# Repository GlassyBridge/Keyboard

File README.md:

<h1 align="center"> MK-1000 </h1>
<h4 align="center">A Modular-Wireless Keyboard </h4>
<div align="center">
  
</div>
<p align="center">A fully custom modular keyboard that has both wireless and wired capabilities, uses MX hotswap switches (with per key RGB lighting) and magnetic pogo pin connectors with I2C protocol.</p>
<h2></h2>
<h2> Features </h2>

- Works over USB-C (wired) or Bluetooth (wireless)
- Integrated magnetic pogo pins for stable I2C connection and adding external modules (numberpads, macropads or OLED modules)
- Integrated charging circuit for portability and wireless operation
- Uses MX hotswap sockets for key switch connections
- Features SK6812MINI-E back mounted LEDs for customizable per key RGB lighting
- Includes a dedicated SWD interface for debugging and development
- A dedicated slide switch to manage battery life

<h2> Why this project? </h2>

This project was made as an attempt to tackle more complex hardware from my previous projects. I spent a lot of time designing and reiterating it and its purpose is simple. I made it to function as a plug and play device that has modular capabilities.

I also wanted a cool looking keyboard so I added features I liked into this one big project.

<h2>Design</h2>
<h3>Schematic</h3>

<h4 align="center">Main board & Keypad</h4>
<h3>PCB</h3>

<h4 align="center">PCB back</h4>

<h4 align="center">PCB front</h4>

<h4 align="center">PCB</h4>

<h4 align="center">PCB 3D model</h4>

<h4 align="center">PCB 3D model with components</h4>

<h4 align="center">Wiring Diagram</h4>

<h2>Firmware</h2>

Available in the `Firmware` folder. (Basic version for now. I'll update it once I built the keyboard)
<h2>Bill of Materials</h2>

| Name                     | Reference   |    Qty     | moq | Price ($) | Shipping   |                                            Link                                             |
| ------------------------ | ----------- | :--------: | --- | --------- | ---------- | :-----------------------------------------------------------------------------------------: |
| OLED Screens (128X32)    | Brd11       |     1      | 1   | 2.42      | Aliexpress |             [Aliexpress](https://www.aliexpress.us/item/3256806165075447.html)              |
| ------------ (128X64)    | Brd12       |     1      | 1   | 4.18      | Aliexpress |             [Aliexpress](https://www.aliexpress.us/item/3256810159598938.html)              |
| 1X6 Magnetic Pogo Pins   | Conn1-Conn8 | 8(4 pairs) | 5p  | 25.25     | Aliexpress |             [Aliexpress](https://www.aliexpress.us/item/3256805098127227.html)              |
| Capacitors (10uF)        | C1-C4       |     4      | 20  | 0.43      | LCSC       |                  [C15850](https://www.lcsc.com/product-detail/C15850.html)                  |
| ---------- (4.7uF)       | C5,C6       |     2      | 20  | 0.29      | LCSC       |                   [C1779](https://www.lcsc.com/product-detail/C1779.html)                   |
| ---------- (22uF)        | C7,C8       |     2      | 20  | 1.12      | LCSC       |                  [C12891](https://www.lcsc.com/product-detail/C12891.html)                  |
| Diodes                   | D1-D99      |     99     | 100 | 0.93      | LCSC       |                   [C2099](https://www.lcsc.com/product-detail/C2099.html)                   |
| ---------- (SS34)        | SS34        |     1      | 20  | 0.56      | LCSC       |                 [C908680](https://www.lcsc.com/product-detail/C908680.html)                 |
| ESDA5V3L                 | ESD1,ESD2   |     2      | 10  | 0.39      | LCSC       |                 [C587142](https://www.lcsc.com/product-detail/C587142.html)                 |
| USB Connector            | J1          |     1      | 5   | 0.84      | LCSC       |                 [C165948](https://www.lcsc.com/product-detail/C165948.html)                 |
| 2x3 1mm PinHeader        | J2          |     1      | 20  | 0.65      | LCSC       |                [C6837603](https://www.lcsc.com/product-detail/C6837603.html)                |
| Inductors  (10uH)        | L1          |     1      | 10  | 0.47      | LCSC       |                  [C88173](https://www.lcsc.com/product-detail/C88173.html)                  |
| ---------- (22uH)        | L2          |     1      | 5   | 0.83      | LCSC       |                  [C27442](https://www.lcsc.com/product-detail/C27442.html)                  |
| SK6812MINI-E (LEDs)      | LED1-LED99  |     99     | 100 | 7.45      | LCSC       |                [C5149201](https://www.lcsc.com/product-detail/C5149201.html)                |
| P_Mosfets                | Q1-Q3       |     3      | 10  | 0.65      | LCSC       |                  [C10487](https://www.lcsc.com/product-detail/C10487.html)                  |
| Resistors  (110K)        | R1          |     2      | 100 | 0.19      | LCSC       |                [C2907221](https://www.lcsc.com/product-detail/C2907221.html)                |
| ---------- (5K1)         | R2,R4       |     2      | 100 | 0.24      | LCSC       |                  [C27834](https://www.lcsc.com/product-detail/C27834.html)                  |
| ---------- (100K)        | R3,R5,R6    |     2      | 100 | 0.22      | LCSC       |                [C2933502](https://www.lcsc.com/product-detail/C2933502.html)                |
| ---------- (4K7)         | R7,R12,R18  |     4      | 100 | 0.19      | LCSC       |                  [C17673](https://www.lcsc.com/product-detail/C17673.html)                  |
| ---------- (27R)         | R8,R11      |     2      | 100 | 0.22      | LCSC       |                  [C17594](https://www.lcsc.com/product-detail/C17594.html)                  |
| ---------- (806K)        | R9,R16,R21  |     3      | 100 | 0.22      | LCSC       |                [C2933502](https://www.lcsc.com/product-detail/C2933502.html)                |
| ---------- (2M)          | R10,R17,R22 |     3      | 100 | 0.30      | LCSC       |                  [C26112](https://www.lcsc.com/product-detail/C26112.html)                  |
| ---------- (15K)         | R13         |     1      | 100 | 0.21      | LCSC       |                [C2930170](https://www.lcsc.com/product-detail/C2930170.html)                |
| ---------- (10K)         | R14,R19     |     2      | 100 | 0.25      | LCSC       |                  [C17414](https://www.lcsc.com/product-detail/C17414.html)                  |
| ---------- (2K)          | R15         |     1      | 100 | 0.25      | LCSC       |                  [C17604](https://www.lcsc.com/product-detail/C17604.html)                  |
| Rotary Encoder           | RE1         |     1      | 1   | 1.87      | LCSC       |                 [C470742](https://www.lcsc.com/product-detail/C470742.html)                 |
| Slide switch (1825232-1) | SPDT1       |     1      | 1   | 0.93      | LCSC       |                [C5167252](https://www.lcsc.com/product-detail/C5167252.html)                |
| MT3608                   | U1          |     1      | 10  | 0.79      | LCSC       |                  [C84817](https://www.lcsc.com/product-detail/C84817.html)                  |
| USB6B1                   | U2          |     1      | 1   | 0.47      | LCSC       |                 [C283483](https://www.lcsc.com/product-detail/C283483.html)                 |
| MDBT50Q-1MV2 (MCU)       | U3          |     1      | 1   | 10.10     | SEED       | [Seed Studio](https://www.seeedstudio.com/MDBT50Q-1M-nRF52840-Based-BLE-Module-p-3147.html) |
| MCP73831T-2ACI/OT        | U4          |     1      | 1   | 0.74      | LCSC       |                 [C424093](https://www.lcsc.com/product-detail/C424093.html)                 |
| XIAO-nRF52840-SMD (MCU)  | U5          |     1      | 1   | 9.90      | 3.75       |       [Seed Studio](https://www.seeedstudio.com/Seeed-XIAO-BLE-nRF52840-p-5201.html)        |
| MCP23017                 | U6          |     1      | 1   | 2.03      | LCSC       |                 [C639770](https://www.lcsc.com/product-detail/C639770.html)                 |
| 74LV1T08GV               | U7,U8       |     2      | 1   | 2.12      | LCSC       |                 [C547934](https://www.lcsc.com/product-detail/C547934.html)                 |
| Keys ----- (Sockets)     | SW1-SW99    |     99     | 110 | 8.18      | Aliexpress |             [Aliexpress](https://www.aliexpress.us/item/3256809001207500.html)              |
| ---------- (Switches)    | -           |     99     | 105 | 21.85 (T) | Aliexpress |             [Aliexpress](https://www.aliexpress.us/item/3256807647145642.html)              |
| ---------- (Key Caps)    | -           |     99     | -   | 7.48 (T)  | Aliexpress |             [Aliexpress](https://www.aliexpress.us/item/3256808975886837.html)              |
| ---------- (Stabilizers) | -           |     5      | -   | 5.78 (T)  | Aliexpress |             [Aliexpress](https://www.aliexpress.us/item/3256801499984864.html)              |
| lithium batteries        | -           |     2      | -   | 18.16 (T) | Aliexpress |             [Aliexpress](https://www.aliexpress.us/item/3256811743915654.html)              |

> *T for total price

| Supplier   | cost  | Shipping | Total cost |
| ---------- | ----- | -------- | ---------- |
| LCSC       | 24.65 | 13.08    | 37.73      |
| Aliexpress | 93.30 | 2.69     | 96.44      |
| SEED       | 20    | 8.55     | 28.55      |
| JLCPCB     | 29.90 | 20.14    | 50.04      |
| Total      | -     | -        | 212.76     |

<h2>Keyboard Case</h2>

A very basic case is provided in the `CAD` folder.

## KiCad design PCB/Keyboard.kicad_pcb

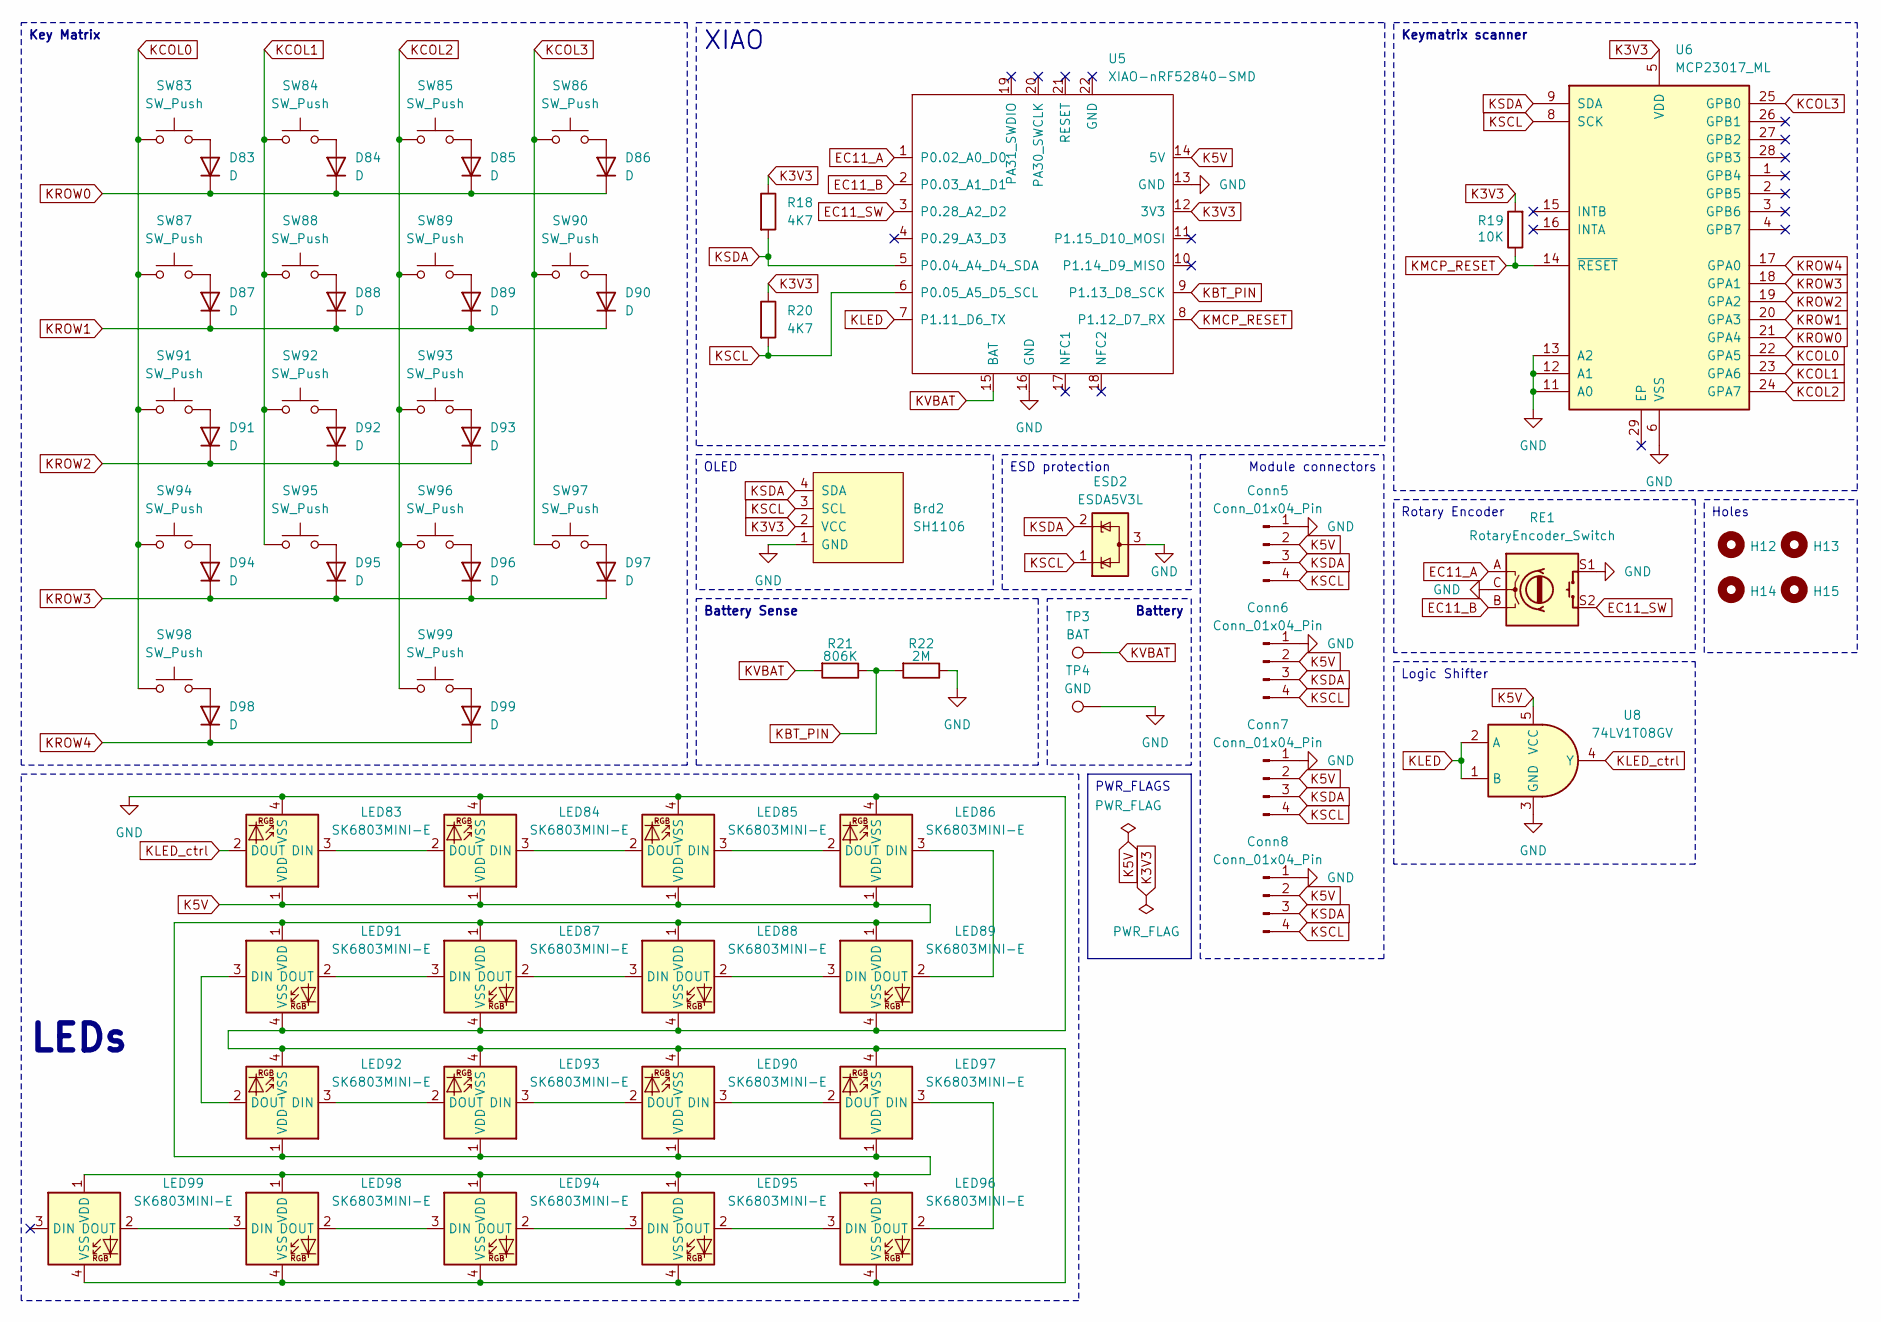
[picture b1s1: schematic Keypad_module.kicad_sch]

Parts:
Brd2: SH1106; 128x64OLED
Conn5, Conn7: Conn_01x04_Pin; Pogopin_Conn_1x4_Female
Conn6, Conn8: Conn_01x04_Pin; Pogopin_Conn_1x4_Male
D83, D84, D85, D86, D87, D88, D89, D90, D91, D92, D93, D94, D95, D96, D97, D98, D99: D; D_SOD-123; LCSC Part # C2099
ESD2: ESDA5V3L; SOT-23-3; LCSC Part # C587142
H12, H13, H14, H15: MountingHole; MountingHole_3.2mm_M3
LED83, LED84, LED85, LED86, LED87, LED88, LED89, LED90, LED91, LED92, LED93, LED94, LED95, LED96, LED97, LED98, LED99: SK6803MINI-E; LED
R18, R20: 4K7; R_0805_2012Metric; LCSC Part # C17673
R19: 10K; R_0805_2012Metric; LCSC Part # C17414
R21: 806K; R_0805_2012Metric; LCSC Part # C2933502
R22: 2M; R_0805_2012Metric; LCSC Part # C26112
RE1: RotaryEncoder_Switch; RotaryEncoder_Alps_EC11E-Switch_Vertical_H20mm_CircularMoun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
SW83, SW84, SW85, SW86, SW87, SW88, SW89, SW91, SW92, SW93, SW94, SW95, SW96, SW99: SW_Push; MX_HS_1u; LCSC Part # C5333465
SW90, SW97: SW_Push; MX_HS_2u_90deg; LCSC Part # C5333465
SW98: SW_Push; MX_HS_2u; LCSC Part # C5333465
TP3: BAT; TestPoint_Pad_D2.0mm
TP4: GND; TestPoint_Pad_D2.0mm
U5: XIAO-nRF52840-SMD; modified-XIAO-nRF52840-SMD; LCSC Part # C37327670
U6: MCP23017_ML; QFN-28-1EP_6x6mm_P0.65mm_EP4.25x4.25mm; LCSC Part # C639770
U8: 74LV1T08GV; SC-74A-5_1.55x2.9mm_P0.95mm

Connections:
EC11_A: RE1.A, U5.1 (P0.02_A0_D0)
EC11_B: RE1.B, U5.2 (P0.03_A1_D1)
EC11_SW: RE1.S2, U5.3 (P0.28_A2_D2)
GND: Brd2.1 (GND), Conn5.1, Conn6.1, Conn7.1, Conn8.1, ESD2.3 (A), LED83.4 (VSS), LED84.4 (VSS), LED85.4 (VSS), LED86.4 (VSS), LED87.4 (VSS), LED88.4 (VSS), LED89.4 (VSS), LED90.4 (VSS), LED91.4 (VSS), LED92.4 (VSS), LED93.4 (VSS), LED94.4 (VSS), LED95.4 (VSS), LED96.4 (VSS), LED97.4 (VSS), LED98.4 (VSS), LED99.4 (VSS), R22.1, RE1.C, RE1.S1, TP4.1, U5.13 (GND), U5.16 (GND), U6.6 (VSS), U6.11 (A0), U6.12 (A1), U6.13 (A2), U8.3 (GND); also elsewhere on the board
K3V3: Brd2.2 (VCC), R18.1, R19.2, R20.1, U5.12 (3V3), U6.5 (VDD)
K5V: Conn5.2, Conn6.2, Conn7.2, Conn8.2, LED83.1 (VDD), LED84.1 (VDD), LED85.1 (VDD), LED86.1 (VDD), LED87.1 (VDD), LED88.1 (VDD), LED89.1 (VDD), LED90.1 (VDD), LED91.1 (VDD), LED92.1 (VDD), LED93.1 (VDD), LED94.1 (VDD), LED95.1 (VDD), LED96.1 (VDD), LED97.1 (VDD), LED98.1 (VDD), LED99.1 (VDD), U5.14 (5V), U8.5 (VCC)
KBT_PIN: R21.1, R22.2, U5.9 (P1.13_D8_SCK)
KCOL0: SW83.1, SW87.1, SW91.1, SW94.1, SW98.1, U6.22 (GPA5)
KCOL1: SW84.1, SW88.1, SW92.1, SW95.1, U6.23 (GPA6)
KCOL2: SW85.1, SW89.1, SW93.1, SW96.1, SW99.1, U6.24 (GPA7)
KCOL3: SW86.1, SW90.1, SW97.1, U6.25 (GPB0)
KLED: U5.7 (P1.11_D6_TX), U8.1 (B), U8.2 (A)
KLED_ctrl: LED83.2 (DOUT), U8.4 (Y)
KMCP_RESET: R19.1, U5.8 (P1.12_D7_RX), U6.14 (~RESET)
KROW0: D83.1 (K), D84.1 (K), D85.1 (K), D86.1 (K), U6.21 (GPA4)
KROW1: D87.1 (K), D88.1 (K), D89.1 (K), D90.1 (K), U6.20 (GPA3)
KROW2: D91.1 (K), D92.1 (K), D93.1 (K), U6.19 (GPA2)
KROW3: D94.1 (K), D95.1 (K), D96.1 (K), D97.1 (K), U6.18 (GPA1)
KROW4: D98.1 (K), D99.1 (K), U6.17 (GPA0)
KSCL: Brd2.3 (SCL), Conn5.4, Conn6.4, Conn7.4, Conn8.4, ESD2.1 (K), R20.2, U5.6 (P0.05_A5_D5_SCL), U6.8 (SCK)
KSDA: Brd2.4 (SDA), Conn5.3, Conn6.3, Conn7.3, Conn8.3, ESD2.2 (K), R18.2, U5.5 (P0.04_A4_D4_SDA), U6.9 (SDA)
KVBAT: R21.2, TP3.1, U5.15 (BAT)
unnamed: D83.2 (A), SW83.2
unnamed: D84.2 (A), SW84.2
unnamed: D85.2 (A), SW85.2
unnamed: D86.2 (A), SW86.2
unnamed: D87.2 (A), SW87.2
unnamed: D88.2 (A), SW88.2
unnamed: D89.2 (A), SW89.2
unnamed: D90.2 (A), SW90.2
unnamed: D91.2 (A), SW91.2
unnamed: D92.2 (A), SW92.2
unnamed: D93.2 (A), SW93.2
unnamed: D94.2 (A), SW94.2
unnamed: D95.2 (A), SW95.2
unnamed: D96.2 (A), SW96.2
unnamed: D97.2 (A), SW97.2
unnamed: D98.2 (A), SW98.2
unnamed: D99.2 (A), SW99.2
unnamed: LED83.3 (DIN), LED84.2 (DOUT)
unnamed: LED84.3 (DIN), LED85.2 (DOUT)
unnamed: LED85.3 (DIN), LED86.2 (DOUT)
unnamed: LED86.3 (DIN), LED89.2 (DOUT)
unnamed: LED87.3 (DIN), LED91.2 (DOUT)
unnamed: LED87.2 (DOUT), LED88.3 (DIN)
unnamed: LED88.2 (DOUT), LED89.3 (DIN)
unnamed: LED90.3 (DIN), LED97.2 (DOUT)
unnamed: LED90.2 (DOUT), LED93.3 (DIN)
unnamed: LED91.3 (DIN), LED92.2 (DOUT)
unnamed: LED92.3 (DIN), LED93.2 (DOUT)
unnamed: LED94.3 (DIN), LED98.2 (DOUT)
unnamed: LED94.2 (DOUT), LED95.3 (DIN)
unnamed: LED95.2 (DOUT), LED96.3 (DIN)
unnamed: LED96.2 (DOUT), LED97.3 (DIN)
unnamed: LED98.3 (DIN), LED99.2 (DOUT)

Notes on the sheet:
ESD protection
Keymatrix scanner
Logic Shifter
LEDs
PWR_FLAGS
Module connectors
Key Matrix
XIAO
Holes
Battery Sense
Battery
OLED
Rotary Encoder

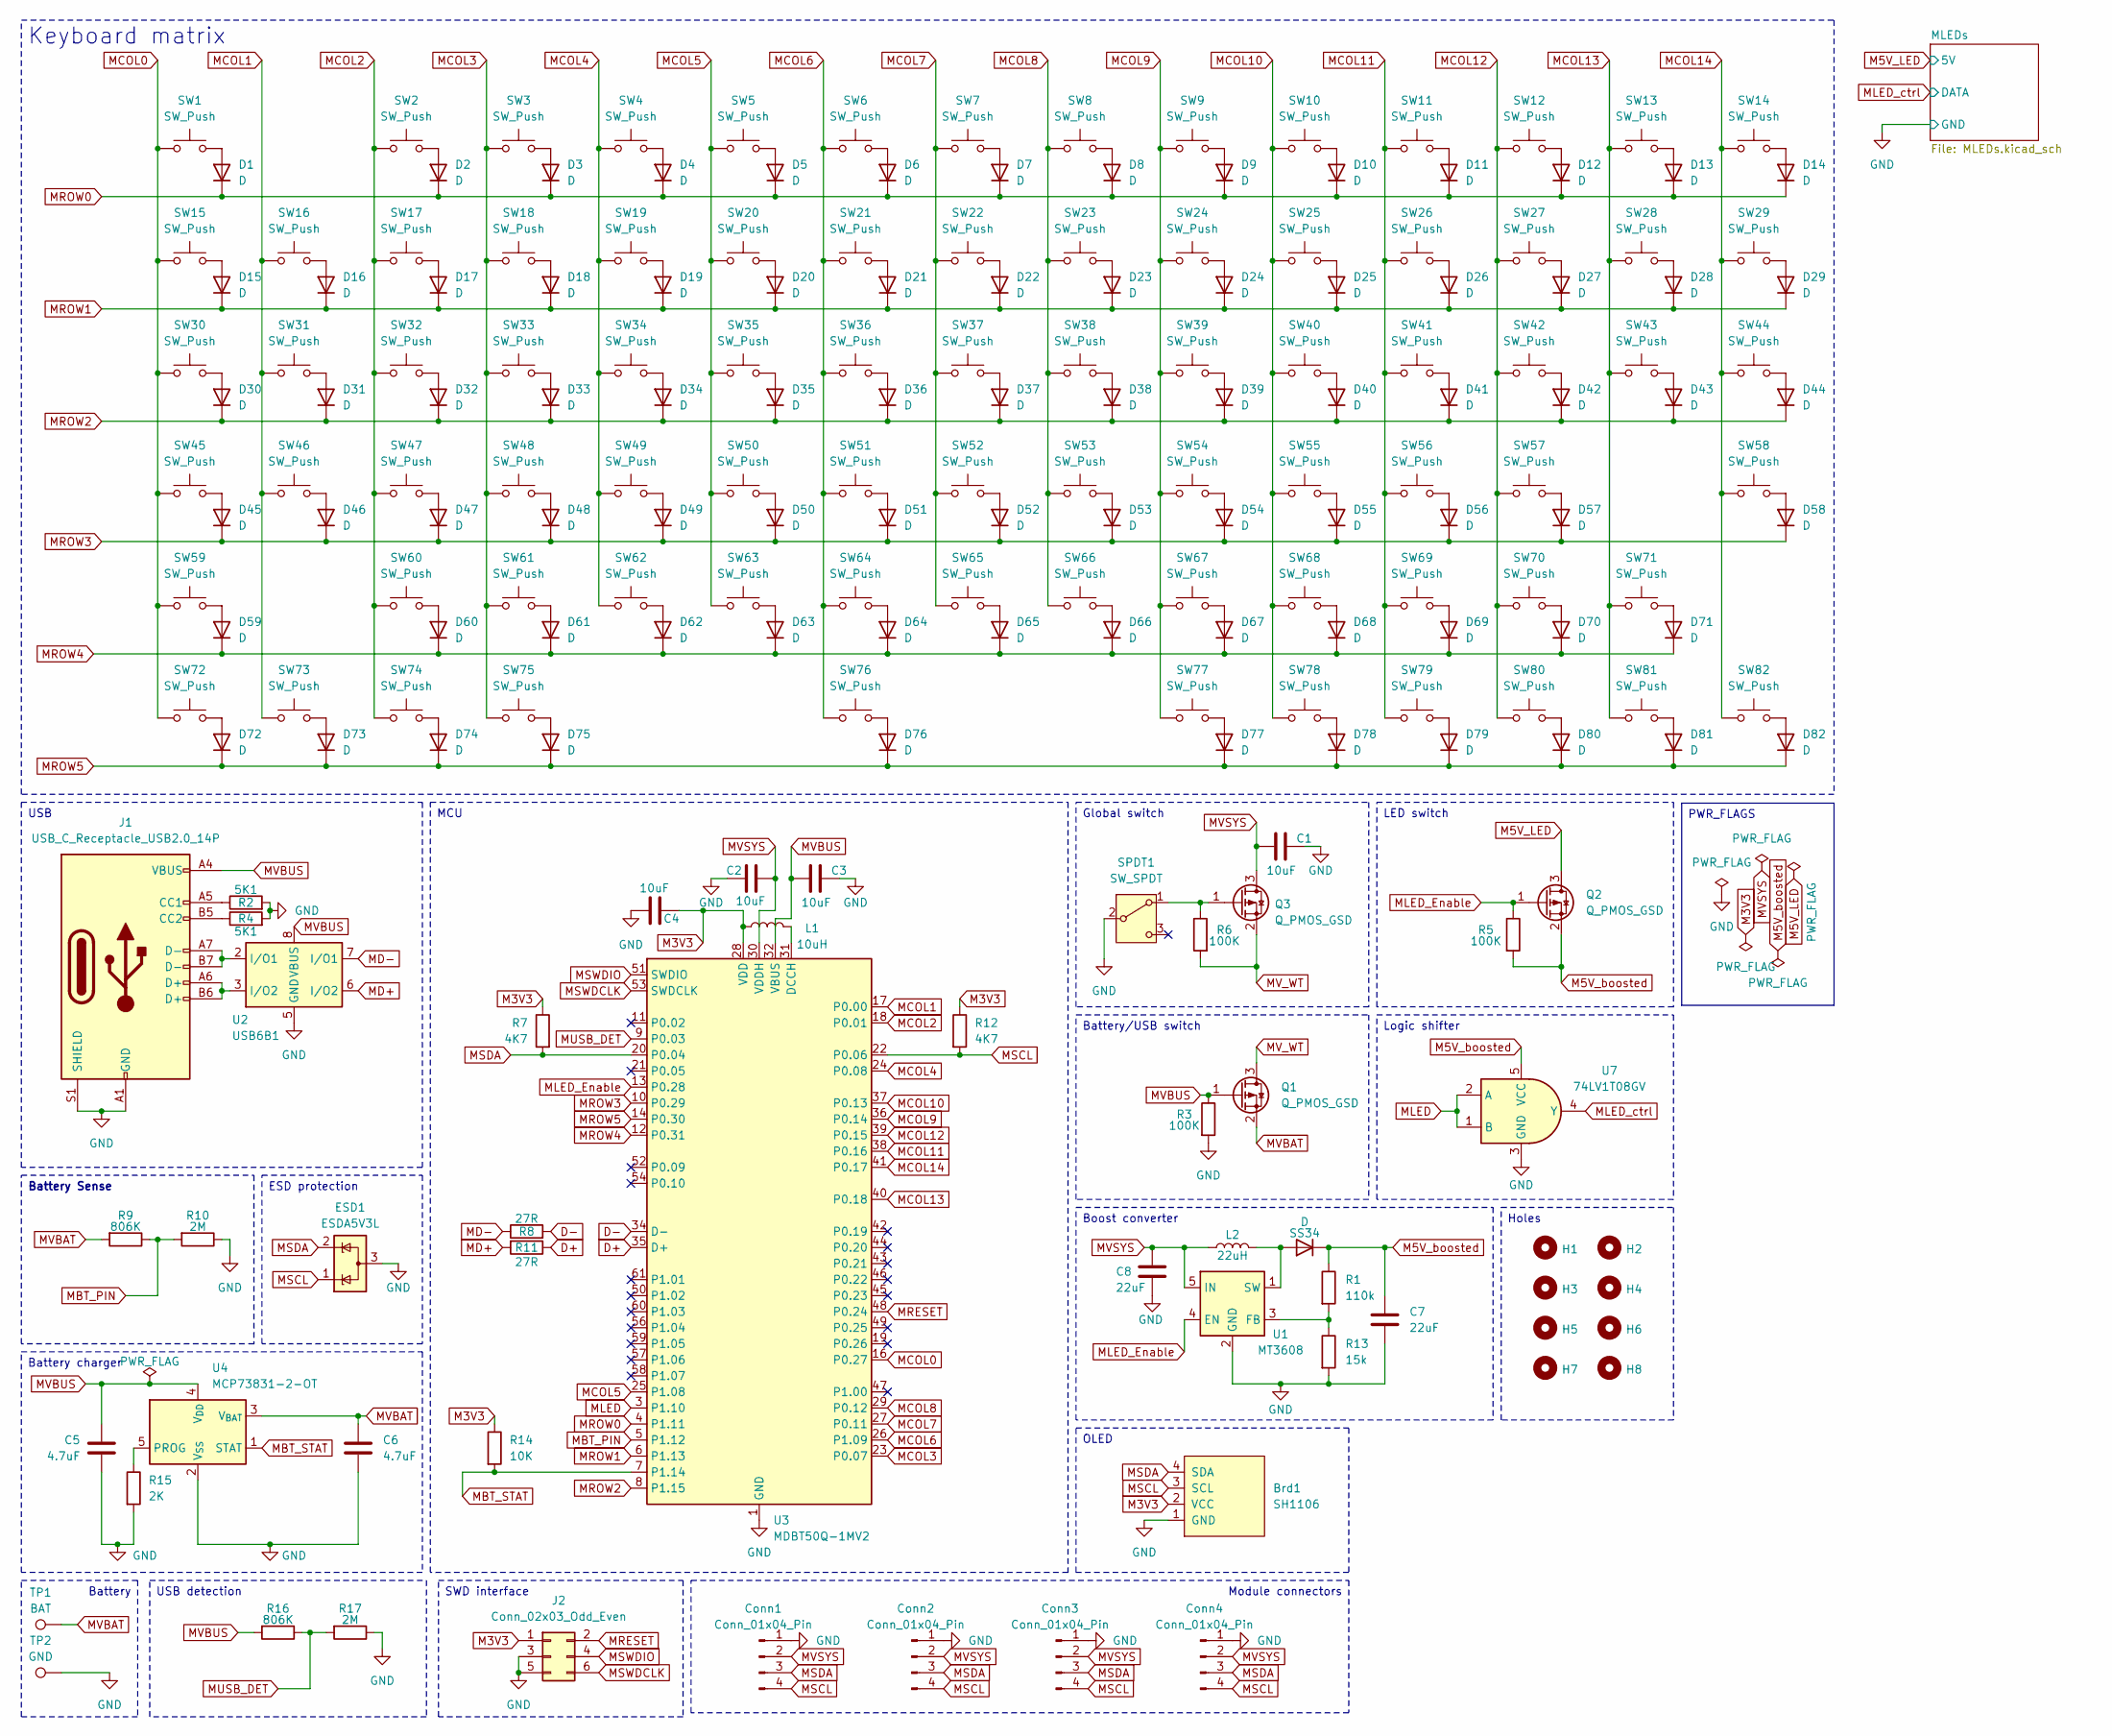
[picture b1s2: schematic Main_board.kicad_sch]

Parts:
Brd1: SH1106; OLED-TH_L38.0-W12.0_HS91L02W2C01
C1, C2, C3, C4: 10uF; C_0805_2012Metric; LCSC Part # C15850
C5, C6: 4.7uF; C_0805_2012Metric; LCSC Part # C1779
C7, C8: 22uF; C_1206_3216Metric
Conn1, Conn3: Conn_01x04_Pin; Pogopin_Conn_1x4_Female
Conn2, Conn4: Conn_01x04_Pin; Pogopin_Conn_1x4_Male
D1, D2, D3, D4, D5, D6, D7, D8, D9, D10, D11, D12, D13, D14, D15, D16, D17, D18, D19, D20, D21, D22, D23, D24, D25, D26, D27, D28, D29, D30, D31, D32, D33, D34, D35, D36, D37, D38, D39, D40, D41, D42, D43, D44, D45, D46, D47, D48, D49, D50, D51, D52, D53, D54, D55, D56, D57, D58, D59, D60, D61, D62, D63, D64, D65, D66, D67, D68, D69, D70, D71, D72, D73, D74, D75, D76, D77, D78, D79, D80, D81, D82: D; D_SOD-123; LCSC Part # C2099
ESD1: ESDA5V3L; SOT-23-3; LCSC Part # C587142
H1, H2, H3, H4, H5, H6, H7, H8: MountingHole; MountingHole_3.2mm_M3
J1: USB_C_Receptacle_USB2.0_14P; USB_C_Receptacle_HRO_TYPE-C-31-M-12; LCSC Part # C165948
J2: Conn_02x03_Odd_Even; PinHeader_2x03_P1.00mm_Vertical; LCSC Part # C6837603
L1: 10uH; L_0805_2012Metric
L2: 22uH; IND-SMD_L7.1-W6.6
Q1, Q2, Q3: Q_PMOS_GSD; SOT-23; LCSC Part # C10487
R1: 110k; R_0805_2012Metric
R2, R4: 5K1; R_0805_2012Metric; LCSC Part # C27834
R3, R5, R6: 100K; R_0805_2012Metric; LCSC Part # C2933502
R7, R12: 4K7; R_0805_2012Metric; LCSC Part # C17673
R8, R11: 27R; R_0805_2012Metric; LCSC Part # C17594
R9, R16: 806K; R_0805_2012Metric; LCSC Part # C2933502
R10, R17: 2M; R_0805_2012Metric; LCSC Part # C26112
R13: 15k; R_0805_2012Metric
R14: 10K; R_0805_2012Metric; LCSC Part # C17414
R15: 2K; R_0805_2012Metric; LCSC Part # C17604
SPDT1: SW_SPDT; 1825232-1
SS34: D; SS34
SW1, SW2, SW3, SW4, SW5, SW6, SW7, SW8, SW9, SW10, SW11, SW12, SW13, SW14, SW15, SW16, SW17, SW18, SW19, SW20, SW21, SW22, SW23, SW24, SW25, SW26, SW27, SW29, SW31, SW32, SW33, SW34, SW35, SW36, SW37, SW38, SW39, SW40, SW41, SW42, SW44, SW46, SW47, SW48, SW49, SW50, SW51, SW52, SW53, SW54, SW55, SW56, SW58, SW60, SW61, SW62, SW63, SW64, SW65, SW66, SW67, SW68, SW69, SW71, SW72, SW73, SW74, SW75, SW77, SW78, SW79, SW80, SW81, SW82: SW_Push; MX_HS_1u; LCSC Part # C5333465
SW28: SW_Push; MX_HS_2u; LCSC Part # C5333465
SW30, SW43: SW_Push; MX_HS_1.5u; LCSC Part # C5333465
SW45, SW70: SW_Push; MX_HS_1.75u; LCSC Part # C5333465
SW57, SW59: SW_Push; MX_HS_2.25u; LCSC Part # C5333465
SW76: SW_Push; MX_HS_6u; LCSC Part # C5333465
TP1: BAT; TestPoint_Pad_D2.0mm
TP2: GND; TestPoint_Pad_D2.0mm
U1: MT3608; SOT-23-6
U2: USB6B1; SOIC-8_3.9x4.9mm_P1.27mm; LCSC Part # C283483
U3: MDBT50Q-1MV2; Raytac_MDBT50Q; LCSC Part # C5118826
U4: MCP73831-2-OT; SOT-23-5; LCSC Part # C424093
U7: 74LV1T08GV; SC-74A-5_1.55x2.9mm_P0.95mm

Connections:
D+: R11.1, U3.35 (D+)
D-: R8.2, U3.34 (D-)
GND: Brd1.1 (GND), C1.2, C2.2, C3.2, C4.1, C5.2, C6.2, C7.2, C8.2, Conn1.1, Conn2.1, Conn3.1, Conn4.1, ESD1.3 (A), J1.A1 (GND), J1.A12 (GND), J1.B1 (GND), J1.B12 (GND), J1.S1 (SHIELD), J2.3, J2.5, R2.2, R3.2, R4.2, R10.1, R13.2, R15.2, R17.1, SPDT1.2 (B), TP2.1, U1.2 (GND), U2.4 (GND), U2.5 (GND), U3.1 (GND), U3.2 (GND), U3.15 (GND), U3.33 (GND), U3.55 (GND), U4.2 (V_{SS}), U7.3 (GND); also elsewhere on the board
M3V3: Brd1.2 (VCC), C4.2, J2.1, L1.1, R7.1, R12.1, R14.1, U3.28 (VDD)
M5V_LED: Q2.3 (D); also elsewhere on the board
M5V_boosted: C7.1, Q2.2 (S), R1.1, R5.2, SS34.1 (K), U7.5 (VCC)
MBT_PIN: R9.1, R10.2, U3.5 (P1.12)
MBT_STAT: R14.2, U3.7 (P1.14), U4.1 (STAT)
MCOL0: SW1.1, SW15.1, SW30.1, SW45.1, SW59.1, SW72.1, U3.16 (P0.27)
MCOL1: SW16.1, SW31.1, SW46.1, SW73.1, U3.17 (P0.00)
MCOL2: SW2.1, SW17.1, SW32.1, SW47.1, SW60.1, SW74.1, U3.18 (P0.01)
MCOL3: SW3.1, SW18.1, SW33.1, SW48.1, SW61.1, SW75.1, U3.23 (P0.07)
MCOL4: SW4.1, SW19.1, SW34.1, SW49.1, SW62.1, U3.24 (P0.08)
MCOL5: SW5.1, SW20.1, SW35.1, SW50.1, SW63.1, U3.25 (P1.08)
MCOL6: SW6.1, SW21.1, SW36.1, SW51.1, SW64.1, SW76.1, U3.26 (P1.09)
MCOL7: SW7.1, SW22.1, SW37.1, SW52.1, SW65.1, U3.27 (P0.11)
MCOL8: SW8.1, SW23.1, SW38.1, SW53.1, SW66.1, U3.29 (P0.12)
MCOL9: SW9.1, SW24.1, SW39.1, SW54.1, SW67.1, SW77.1, U3.36 (P0.14)
MCOL10: SW10.1, SW25.1, SW40.1, SW55.1, SW68.1, SW78.1, U3.37 (P0.13)
MCOL11: SW11.1, SW26.1, SW41.1, SW56.1, SW69.1, SW79.1, U3.38 (P0.16)
MCOL12: SW12.1, SW27.1, SW42.1, SW57.1, SW70.1, SW80.1, U3.39 (P0.15)
MCOL13: SW13.1, SW28.1, SW43.1, SW71.1, SW81.1, U3.40 (P0.18)
MCOL14: SW14.1, SW29.1, SW44.1, SW58.1, SW82.1, U3.41 (P0.17)
MD+: R11.2, U2.6 (I/O2)
MD-: R8.1, U2.7 (I/O1)
MLED: U3.3 (P1.10), U7.1 (B), U7.2 (A)
MLED_Enable: Q2.1 (G), R5.1, U1.4 (EN), U3.13 (P0.28)
MLED_ctrl: U7.4 (Y); also elsewhere on the board
MRESET: J2.2, U3.48 (P0.24)
MROW0: D1.1 (K), D2.1 (K), D3.1 (K), D4.1 (K), D5.1 (K), D6.1 (K), D7.1 (K), D8.1 (K), D9.1 (K), D10.1 (K), D11.1 (K), D12.1 (K), D13.1 (K), D14.1 (K), U3.4 (P1.11)
MROW1: D15.1 (K), D16.1 (K), D17.1 (K), D18.1 (K), D19.1 (K), D20.1 (K), D21.1 (K), D22.1 (K), D23.1 (K), D24.1 (K), D25.1 (K), D26.1 (K), D27.1 (K), D28.1 (K), D29.1 (K), U3.6 (P1.13)
MROW2: D30.1 (K), D31.1 (K), D32.1 (K), D33.1 (K), D34.1 (K), D35.1 (K), D36.1 (K), D37.1 (K), D38.1 (K), D39.1 (K), D40.1 (K), D41.1 (K), D42.1 (K), D43.1 (K), D44.1 (K), U3.8 (P1.15)
MROW3: D45.1 (K), D46.1 (K), D47.1 (K), D48.1 (K), D49.1 (K), D50.1 (K), D51.1 (K), D52.1 (K), D53.1 (K), D54.1 (K), D55.1 (K), D56.1 (K), D57.1 (K), D58.1 (K), U3.10 (P0.29)
MROW4: D59.1 (K), D60.1 (K), D61.1 (K), D62.1 (K), D63.1 (K), D64.1 (K), D65.1 (K), D66.1 (K), D67.1 (K), D68.1 (K), D69.1 (K), D70.1 (K), D71.1 (K), U3.12 (P0.31)
MROW5: D72.1 (K), D73.1 (K), D74.1 (K), D75.1 (K), D76.1 (K), D77.1 (K), D78.1 (K), D79.1 (K), D80.1 (K), D81.1 (K), D82.1 (K), U3.14 (P0.30)
MSCL: Brd1.3 (SCL), Conn1.4, Conn2.4, Conn3.4, Conn4.4, ESD1.1 (K), R12.2, U3.22 (P0.06)
MSDA: Brd1.4 (SDA), Conn1.3, Conn2.3, Conn3.3, Conn4.3, ESD1.2 (K), R7.2, U3.20 (P0.04)
MSWDCLK: J2.6, U3.53 (SWDCLK)
MSWDIO: J2.4, U3.51 (SWDIO)
MUSB_DET: R16.1, R17.2, U3.9 (P0.03)
MVBAT: C6.1, Q1.2 (S), R9.2, TP1.1, U4.3 (V_{BAT})
MVBUS: C3.1, C5.1, J1.A4 (VBUS), J1.A9 (VBUS), J1.B4 (VBUS), J1.B9 (VBUS), Q1.1 (G), R3.1, R16.2, U2.1 (VBUS), U2.8 (VBUS), U3.32 (VBUS), U4.4 (V_{DD})
MVSYS: C1.1, C2.1, C8.1, Conn1.2, Conn2.2, Conn3.2, Conn4.2, L2.1, Q3.3 (D), U1.5 (IN), U3.30 (VDDH)
MV_WT: Q1.3 (D), Q3.2 (S), R6.2
unnamed: D1.2 (A), SW1.2
unnamed: D2.2 (A), SW2.2
unnamed: D3.2 (A), SW3.2
unnamed: D4.2 (A), SW4.2
unnamed: D5.2 (A), SW5.2
unnamed: D6.2 (A), SW6.2
unnamed: D7.2 (A), SW7.2
unnamed: D8.2 (A), SW8.2
unnamed: D9.2 (A), SW9.2
unnamed: D10.2 (A), SW10.2
unnamed: D11.2 (A), SW11.2
unnamed: D12.2 (A), SW12.2
unnamed: D13.2 (A), SW13.2
unnamed: D14.2 (A), SW14.2
unnamed: D15.2 (A), SW15.2
unnamed: D16.2 (A), SW16.2
unnamed: D17.2 (A), SW17.2
unnamed: D18.2 (A), SW18.2
unnamed: D19.2 (A), SW19.2
unnamed: D20.2 (A), SW20.2
unnamed: D21.2 (A), SW21.2
unnamed: D22.2 (A), SW22.2
unnamed: D23.2 (A), SW23.2
unnamed: D24.2 (A), SW24.2
unnamed: D25.2 (A), SW25.2
unnamed: D26.2 (A), SW26.2
unnamed: D27.2 (A), SW27.2
unnamed: D28.2 (A), SW28.2
unnamed: D29.2 (A), SW29.2
unnamed: D30.2 (A), SW30.2
unnamed: D31.2 (A), SW31.2
unnamed: D32.2 (A), SW32.2
unnamed: D33.2 (A), SW33.2
unnamed: D34.2 (A), SW34.2
unnamed: D35.2 (A), SW35.2
unnamed: D36.2 (A), SW36.2
unnamed: D37.2 (A), SW37.2
unnamed: D38.2 (A), SW38.2
unnamed: D39.2 (A), SW39.2
unnamed: D40.2 (A), SW40.2
unnamed: D41.2 (A), SW41.2
unnamed: D42.2 (A), SW42.2
unnamed: D43.2 (A), SW43.2
unnamed: D44.2 (A), SW44.2
unnamed: D45.2 (A), SW45.2
unnamed: D46.2 (A), SW46.2
unnamed: D47.2 (A), SW47.2
unnamed: D48.2 (A), SW48.2
unnamed: D49.2 (A), SW49.2
unnamed: D50.2 (A), SW50.2
unnamed: D51.2 (A), SW51.2
unnamed: D52.2 (A), SW52.2
unnamed: D53.2 (A), SW53.2
unnamed: D54.2 (A), SW54.2
unnamed: D55.2 (A), SW55.2
unnamed: D56.2 (A), SW56.2
unnamed: D57.2 (A), SW57.2
unnamed: D58.2 (A), SW58.2
unnamed: D59.2 (A), SW59.2
unnamed: D60.2 (A), SW60.2
unnamed: D61.2 (A), SW61.2
unnamed: D62.2 (A), SW62.2
unnamed: D63.2 (A), SW63.2
unnamed: D64.2 (A), SW64.2
unnamed: D65.2 (A), SW65.2
unnamed: D66.2 (A), SW66.2
unnamed: D67.2 (A), SW67.2
unnamed: D68.2 (A), SW68.2
unnamed: D69.2 (A), SW69.2
unnamed: D70.2 (A), SW70.2
unnamed: D71.2 (A), SW71.2
unnamed: D72.2 (A), SW72.2
unnamed: D73.2 (A), SW73.2
unnamed: D74.2 (A), SW74.2
unnamed: D75.2 (A), SW75.2
unnamed: D76.2 (A), SW76.2
unnamed: D77.2 (A), SW77.2
unnamed: D78.2 (A), SW78.2
unnamed: D79.2 (A), SW79.2
unnamed: D80.2 (A), SW80.2
unnamed: D81.2 (A), SW81.2
unnamed: D82.2 (A), SW82.2
unnamed: J1.A5 (CC1), R2.1
unnamed: J1.B5 (CC2), R4.1
unnamed: J1.A6 (D+), J1.B6 (D+), U2.3 (I/O2)
unnamed: J1.A7 (D-), J1.B7 (D-), U2.2 (I/O1)
unnamed: Q3.1 (G), R6.1, SPDT1.1 (A)
unnamed: L2.2, SS34.2 (A), U1.1 (SW)
unnamed: R1.2, R13.1, U1.3 (FB)
unnamed: L1.2, U3.31 (DCCH)
unnamed: R15.1, U4.5 (PROG)

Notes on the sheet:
PWR_FLAGS
USB detection
Battery
Module connectors
Battery charger
Logic shifter
Battery Sense
SWD interface
MCU
OLED
ESD protection
USB
Keyboard matrix
Holes
Boost converter
LED switch
Global switch
Battery/USB switch
